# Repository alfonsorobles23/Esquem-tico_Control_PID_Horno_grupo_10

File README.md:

Se agregaron los códigos utilizados (completo y ordenados en carpeta zip) en el software STM32CubeIDE (05-12-2023) más importantes se agregaron en carpeta git.

Se realizaron los cambios solicitados (03-11-2023).

Se agregó archivos nueva entrega (30-10-2023) en carpeta PCB_Files. Se agregaron los archivos necesarios de igual forma se agregó como carpeta zip todos los archivos del proyecto (Esquematicos_grupo_10) ahi se encuentran los archivos en carpetas ordenadas.

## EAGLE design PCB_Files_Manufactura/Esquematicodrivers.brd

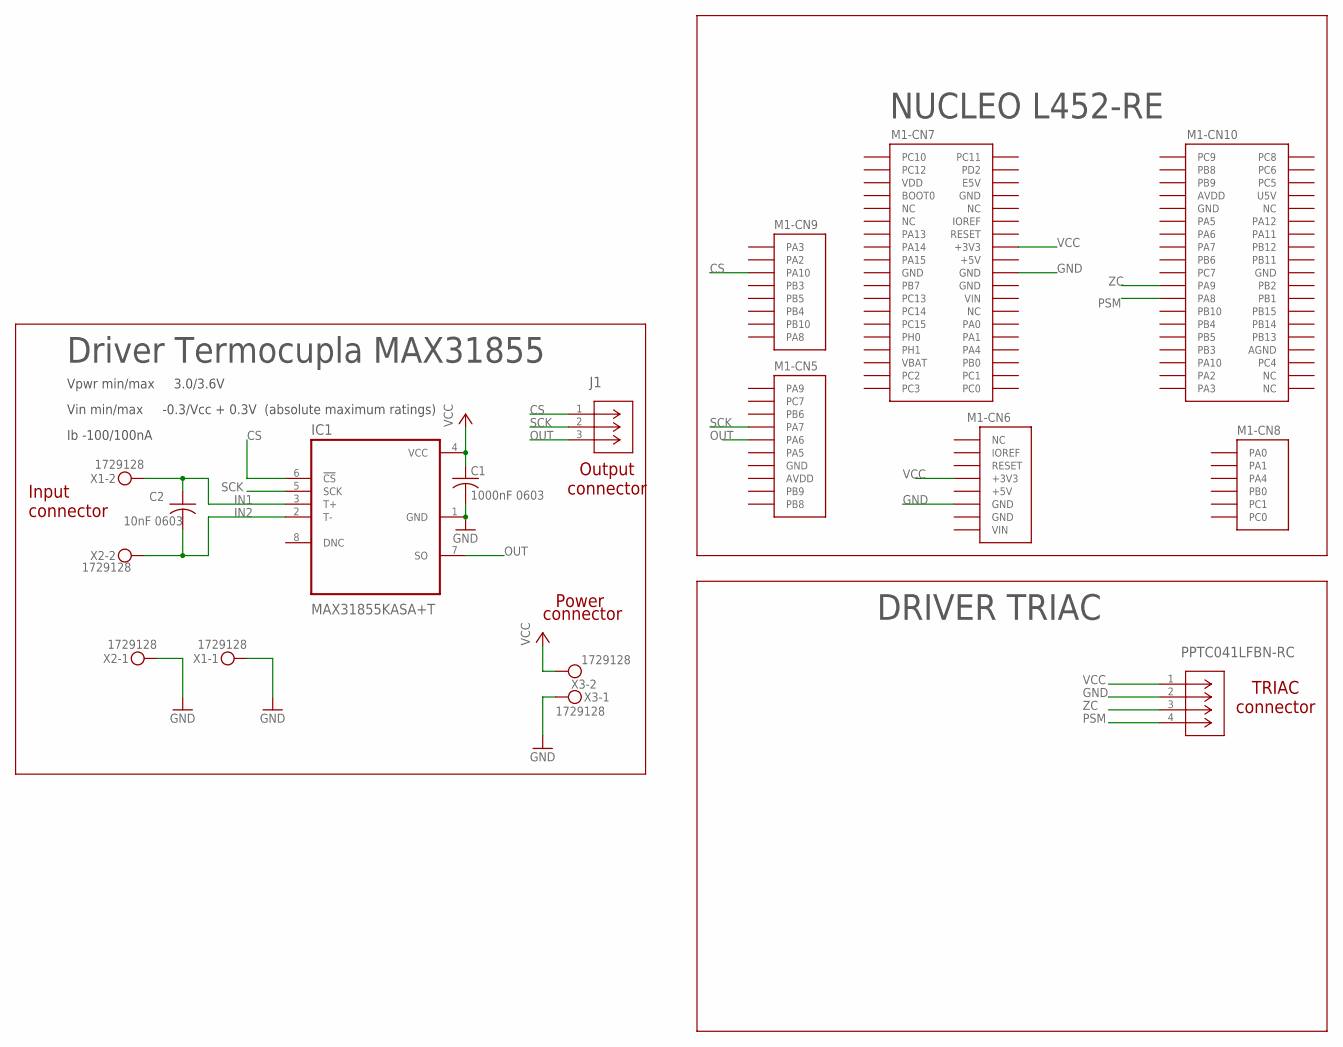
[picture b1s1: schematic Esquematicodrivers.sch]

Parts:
C1: 1000nF 0603; C0603; PARTNO CC0603KRX7R7BB104
C2: 10nF 0603; C0603; PARTNO GRM033R71A103KA01D
IC1: MAX31855KASA+T; SOIC127P600X175-8N; PARTNO MAX31855KASA+T
J1: PPPC031LFBN-RCCONN_PPPC031LFBN-RC_SUL; CONN_PPPC031LFBN-RC_SUL; PARTNO PPPC031LFBN-RC
M1: NUCLEO-L452RE; NUCLEO-64
PPTC041LFBN-RC: PPTC041LFBN-RCCONN_PPTC041LFBN-RC_SUL; CONN_PPTC041LFBN-RC_SUL; PARTNO PPTC041LFBN-RC
X1, X2, X3: 1729128; MKDSN1,5/2-5,08; PARTNO 1729128

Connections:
+5V: M1.CN6-5 (+5V), M1.CN7-18 (+5V)
AGND: M1.CN10-32 (AGND)
AVDD: M1.CN5-8 (AVDD), M1.CN10-7 (AVDD)
CS: IC1.6 (!CS), J1.1, M1.CN9-3 (PA10)
GND: C1.2, IC1.1 (GND), M1.CN5-7 (GND), M1.CN6-6 (GND), M1.CN6-7 (GND), M1.CN7-8 (GND), M1.CN7-19 (GND), M1.CN7-20 (GND), M1.CN7-22 (GND), M1.CN10-9 (GND), M1.CN10-20 (GND), PPTC041LFBN-RC.2 (GND), X1.1, X2.1, X3.1
IN1: C2.1, IC1.3 (T+), X1.2
IN2: C2.2, IC1.2 (T-), X2.2
IOREF: M1.CN6-2 (IOREF)
OUT: IC1.7 (SO), J1.3, M1.CN5-5 (PA6)
PSM: M1.CN10-23 (PA8), PPTC041LFBN-RC.4 (PWM)
SCK: IC1.5 (SCK), J1.2, M1.CN5-4 (PA7)
U5V: M1.CN10-8 (U5V)
VBAT: M1.CN7-33 (VBAT)
VCC: C1.1, IC1.4 (VCC), M1.CN6-4 (+3V3), M1.CN7-16 (+3V3), PPTC041LFBN-RC.1 (VCC), X3.2
VDD: M1.CN7-5 (VDD)
VIN: M1.CN6-8 (VIN), M1.CN7-24 (VIN)
ZC: M1.CN10-21 (PA9), PPTC041LFBN-RC.3 (Z-C)

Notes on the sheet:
Driver Termocupla MAX31855
Vpwr min/max 3.0/3.6V
Vin min/max -0.3/Vcc + 0.3V (absolute maximum ratings)
Ib -100/100nA
Input connector
Power
connector
Output connector
TRIAC connector
NUCLEO L452-RE
DRIVER TRIAC

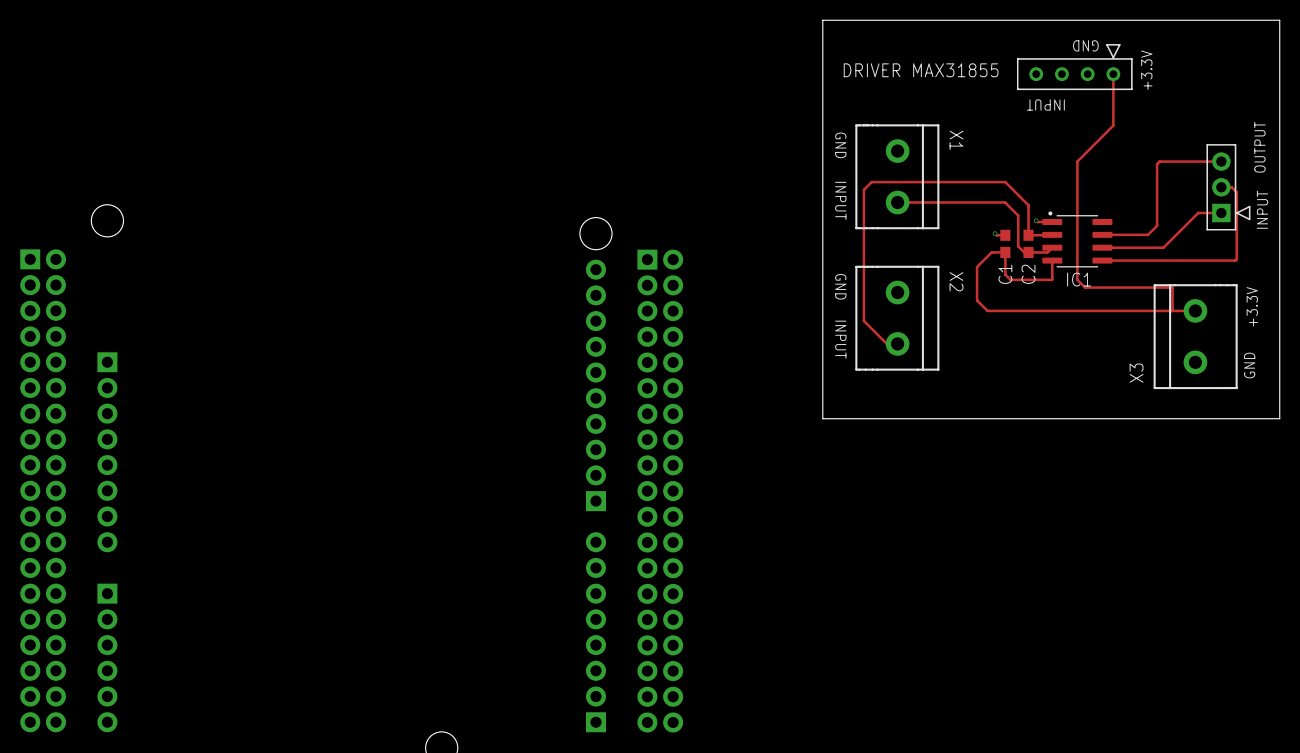
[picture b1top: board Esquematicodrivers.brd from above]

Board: 2 copper layers, 45.1 x 39.4 mm, 9 parts (0 on the bottom side), 12 nets.

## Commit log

2023-10-19 docs
2023-10-30 Create PCB_Archivos_Manufactura
2023-10-30 Rename PCB_Archivos_Manufactura to
2023-12-05 Create nn

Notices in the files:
parts and their libraries:
PPTC041LFBN-RC: COPYRIGHT: Copyright (C) 2023 Ultra Librarian. All rights reserved.
